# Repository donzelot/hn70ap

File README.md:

# hn70ap
Development board for modern packet radio on UHF

This repository contains sources for a few kicad projects and a NuttX board
support package for the board.

The main schematic and additional schematics and board designs are released
under the CERN OHL license.

Prerequisites
=============
 * linux (in 2017 there are many ways to get that)
 * a micro-usb cable to see the debug uart output
 * a jtag/swd adapter
 * a working openocd installation
 * an arm-none-eabi toolchain: https://launchpad.net/gcc-arm-embedded
 * to change the default configs: install kconfig-frontends
 
Mandatory: Install toolchain
============================
The arm-none-eabi toolchain provided by your distro probably does not work OK
(from experience). You may be lucky but this is not widespread enough. So we're
installing a really working toolchain.

The hardest way: compile a toolchain
------------------------------------
Hey this is a beginner guide. you dont need my guide if you are doing that. Help
yourself!

The hard way: download and install
----------------------------------

Open a bash shell console, then type commands ONE BY ONE (adapt them if you know
what you are doing):
```
$ cd $HOME
$ mkdir toolchains
$ cd toolchains
$ wget -O toolchain.tar.bz2 https://launchpad.net/gcc-arm-embedded/5.0/5-2016-q3-update/+download/gcc-arm-none-eabi-5_4-2016q3-20160926-linux.tar.bz2
$ tar jxvf toolchain.tar.bz2
$ cd $HOME
$ export PATH=$PATH:$HOME/toolchains/gcc-arm-none-eabi-5_4-2016q3/bin
```
The last line makes the ARM compiler available in your shell environment. You
can make that automatic, search the web. Otherwise you have to execute this last
line in each new shell window.

The easy way for ubuntu based distros
-------------------------------------

There is a ppa
```
sudo add-apt-repository ppa:team-gcc-arm-embedded/ppa
sudo apt-get update
sudo apt-get install gcc-arm-embedded
```

Toolchain test
--------------

You can test that the toolchain is functional by typing this command and
expecting this answer:
```
$ arm-none-eabi-gcc
arm-none-eabi-gcc: fatal error: no input files
compilation terminated.
```

If the command is not found, then the toolchain is not correctly installed and
the following will NOT work.

Optional: kconfig-frontends
===========================
Skip for now.
TODO, https://bitbucket.org/nuttx/tools, ./configure && make && make install

openocd
=======
Skip for now. TODO apt-get or ./configure && make && make install

Basic Build
===========
You need a working NuttX development environment:

```
$ mkdir nuttx
$ cd nuttx
$ git clone https://bitbucket.org/nuttx/nuttx
$ git clone https://bitbucket.org/nuttx/apps
$ cd nuttx
```
Then you can clone the board config in the proper directory
(This is NOT a submodule!)
```
$ cd configs
$ git clone https://github.com/f4grx/hn70ap
$ cd ..
```

Then choose any of the following test configurations
```
$ tools/configure.sh hn70ap/build/0_boot
```
```
$ tools/configure.sh hn70ap/build/1_memories
```
```
$ tools/configure.sh hn70ap/build/2_oled
```
And build the binary image for this board:
```
$ make
```
This should end up with an ELF binary 'nuttx', and binary images nuttx.bin

You then have to flash this binary on your board, probably with OpenOCD.

This will give you a basic shell, type help to show basic commands. This can be used to validate the behaviour of the board's CPU.

Flashing without JTAG
=====================

This will be possible later, when the bootloader is made ready. The hardware is ready to support that.
A python tool will build an update image from the nuttx elf output, and you will be able to send that image via ethernet or serial.

The bootloader is currently being written. The algorithm is as follows: At CPU startup, the external flash is initialized and searched for a firmware update, except when the button is pressed. If the update is valid, it is applied. If a failure happens, or the button has been pressed, enter a serial download mode. This mode will expect a firmware update image on the serial port and then write it to the external flash. Once done, an update attempt will be attempted after a reboot.

Advanced build
==============
More configurations will be added later that can be used to test ethernet, spi/i2c memories, etc

To modify the nuttx options type make menuconfig and mess around.

To get useful behaviour from this board you will need to add some applications that are not developed yet.

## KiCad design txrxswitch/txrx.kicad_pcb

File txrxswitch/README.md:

This folder contains a complete, stand-alone kicad project for a fast TX/RX switch that could be used with the main hn70ap circuit.

The design is experimental, in particular, I have no idea if isolation between the tx and rx branches is enough.

The project is released under the CERN OHL (schematic and board).

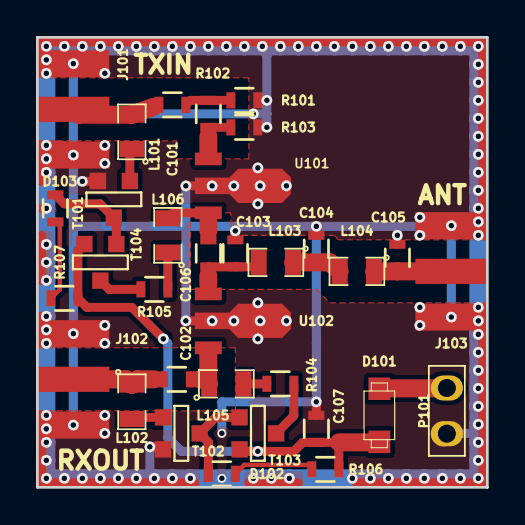
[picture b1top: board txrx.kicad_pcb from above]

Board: 2 copper layers, 25.0 x 25.0 mm, 33 parts (0 on the bottom side), 22 nets.

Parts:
C101, C102, C103, C104, C105, C106, C107: 100p; 0603_m1608
D101: DIODE; SOD123
D102, D103: LED; 0603_m1608
J101, J102, J103: SMA; SMA_EDGE_NRW
L101, L102: 3u3; 0805_m2012
L103, L104, L105, L106: LSMALL; 0805_m2012
P101: CONN_01X02; PINS-2.54-1x2
R101, R102, R103, R104, R105, R106, R107: RSMALL; 0603_m1608
T101, T102: MOSN_SMALL; SOT23GDS
T103, T104: MOSP_SMALL; SOT23GDS
U101: MMIC_SMALL; SOT89
U102: PGA-103+; SOT89

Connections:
GND: C103.1, C104.1, C105.1, C107.1, J101.2, J102.2, J103.2, P101.2, R101.2, R103.2, T101.S, T102.S, U101.2, U102.2
unnamed: C101.1, R101.1, R102.1
unnamed: C101.2, J101.1, L101.2
unnamed: C102.1, L105.1, U102.3
unnamed: C102.2, J102.1, L102.1
unnamed: C103.2, C106.1, L103.2, U102.1
unnamed: C104.2, L103.1, L104.2
unnamed: C105.2, J103.1, L104.1
unnamed: C106.2, L106.2, U101.3
unnamed: D101.A, P101.1
unnamed: D102.1, R106.2
unnamed: D102.2, T102.D, T103.G
unnamed: D103.1, R107.2
unnamed: D103.2, T101.D, T104.G
unnamed: L101.1, T101.G
unnamed: L102.2, T102.G
unnamed: L105.2, R104.1
unnamed: L106.1, R105.2
unnamed: R102.2, R103.1, U101.1
unnamed: R104.2, T103.D
unnamed: R105.1, T104.D
VDD: C107.2, D101.K, R106.1, R107.1, T103.S, T104.S

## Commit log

2017-08-01 Update README.md
    Some explanations to get started
2017-08-01 set licence to bsd 3 clause since
2017-08-01 initial files copied from stm32f429i-disco config with some renames and changes
2017-08-01 the canned config builds
2017-08-01 make Make.defs global
2017-08-01 typos
2017-08-01 Toolchain instructions
2017-08-01 details
2017-08-01 back to home dir
2017-08-01 fix toolchain path
2017-08-01 toolchain test
2017-08-01 easier toolchain options
2017-08-01 Add CERN OHL 1.2 and board readme
2017-08-01 Add existing AP project with dependencies on grx libs
2017-08-01 Remove dependencies on grx SCH libs, all components now in dedicated lib
2017-08-01 Describe the hardware connections
2017-08-01 Fix grid origin
2017-08-01 Removed dependencies on f4libs, project is now fully standalone
2017-08-02 set clock to 180 MHz
2017-08-02 define IRQ and CS lines for both radios
2017-08-02 Define radio IRQ and CS lines in readme
2017-08-02 update irq list in cpu schematic
2017-08-02 Update licence to match github detected templates
2017-08-02 actually add component library, updated with RF4463F30
2017-08-02 add rf4463f30 to radio schematic
2017-08-02 Remove useless configs
2017-08-02 More peripheral definitions
2017-08-02 Finish dual secondary radio schematic including common SDN signal, add RF4463F30 footprint
2017-08-02 Routing SPI bus to radios
2017-08-02 xtal was too close from spi bus
2017-08-02 Move cpu regulator to bring C311 to front, draw mask on back panel edge
2017-08-02 Optimizations
2017-08-03 Improve RF routing around RF4463F30 output
2017-08-03 Details added
2017-08-03 Add LEDs, major work happening in routing.
2017-08-03 add copper border on the right side
2017-08-07 Define correct peripheral pins, disable CCM heap, save latest defconfig
2017-08-07 Update LEDs pinout
2017-08-08 stop making a hex file
2017-08-08 Fix mtd partition initialization
2017-08-08 Add bootloader support and auto versioning
2017-08-09 Add footprint for wurth shielded box 20mm
2017-08-09 WIP rerouting with shielded boxes
2017-08-09 Add a TODOLIST
2017-08-09 add two LEDs for heartbeat and CPU activity
2017-08-09 Added 32khz xtal
2017-08-09 More routing and optimization Routed both CPU XTAL and VBAT connector Improved PSU fitting under shield
2017-08-09 fix RADIO_SDN near CPU pin
2017-08-09 D302 to VDD
2017-08-10 Add an application directory
2017-08-10 Add a directory for application with a readme Move all build defconfigs to their own folder Update main readme according to new folder structure
2017-08-11 Route I2C pullups, improve bottom layer clutter
2017-09-01 fix board so it can be opened with kicad 4.0.7
2017-09-11 add PDF schematic
2017-09-11 placed main radio shield and rerouted SPI bus around
2017-09-11 More SPI routing
2017-09-12 rearrange radio layout
2017-09-12 Update PP45 to use round drills for oshpark
2017-09-12 Finish schematic about RF bias, RF routing complete
2017-09-12 Update PDF schematic
2017-09-12 Missing a GND trace
2017-09-13 Fixed DRC, added ground planes, started via stitching around RF lines
2017-09-22 add a button, rename some nets, add some decoupling caps
2017-09-22 update debug interface power supply for LEDs
2017-09-26 schematic update
2017-09-28 Add pullups to ethernet lines, and re-install ferrite bead on ethernet vdda
2017-09-28 Avoid the use of extvcc, use internal compensation
2017-10-03 add test points for radio spi, add edge launch SMA for radio IO
2017-10-04 add a testpoint on mac_refclk and end launch sma to aux radio
2017-10-05 Add a ferrite bead on Vusb, thanks to f6itu for review
2017-10-05 Fix TX matching according to Silabs AN627
2017-10-26 Add a 5V LDO to power the RF4463
2017-11-24 latest changes
2017-12-01 add an UFL socket to feed an external ref to the onboard si4463
2017-12-01 add a tcxo
2017-12-08 add a test point for main radio CS signal
2017-12-11 add a test pin on IRQ
2017-12-11 add test points on ethernet lines
2017-12-13 final adjustments before paper review
2017-12-14 add gpio test points
2017-12-14 add debug uart test points
2017-12-15 add tx/rx switch project
2017-12-18 tx/rx switch complete
2017-12-21 Update README.md
    Add precisions
2017-12-21 Update README.md
    Add details
2017-12-21 Create README.md
    Add a readme for the switch
2018-01-10 disable ethernet in nsh config, move make.defs
2018-02-09 update defconfig with debug, add ocd tools
2018-02-09 update configuration names, add a readme for build configs
2018-02-10 create the startup blink configuration
2018-02-10 rename board source files add openocd script to reboot board
2018-02-11 The flash works
2018-02-11 Enable I2C3 bus
2018-02-11 add code for i2c eeprom initialization, requires i2cprom branch
2018-02-12 move make.defs to proper place, update config to build ee driver
2018-02-14 Add OLED screen initialization and example app
2018-02-14 remove incorrect includes
2018-02-15 reformat readmes, update information about nuttx configurations and i2c bus
2018-02-16 Add initialization code for radio transceivers
2018-02-16 Create board specific feature enable options
2018-02-16 start bootloader implementation
2018-02-16 cleanup kconfig
2018-02-16 add ethernet boot skeleton from somewhere else
2018-02-16 More stuff to boot ethernet
2018-02-16 Add info about enclosure
2018-02-19 radio init is functional. also more bootloader preparations
2018-02-19 last schematic updates and pdf
2018-02-20 add gpio functions to bootloader
2018-02-20 update both readmes
2018-02-20 fix indentation
2018-02-20 more improvements in gpio
2018-02-20 bootloader now writes a short message before booting user code
2018-02-21 add spi lib for bootloader - update Ethernet config PHY address
2018-02-22 Start a system daemon app to manage hardware status
2018-02-22 Prepare update algorithms
2018-02-23 add aux radio config
2018-02-23 improve spiflash
2018-02-23 build fixes
2018-02-23 read jedec id works
2018-02-23 Started bootloader spec
2018-02-23 finish boot image spec
2018-02-23 precisions and fixes
2018-02-23 fixes
2018-02-23 mkupdate tool generates the same output as objcopy
2018-02-23 finished software update tool
2018-02-23 turn useless status app into updater. add skeletons for firmware update tool and host pc update sender
2018-02-24 light green led at boot prepare mtd access from userspace
2018-02-24 rename LED definitions add MTD ops in mtdchar ioctls remove control of internal leds in the bootloader flash external red during bootloader execution, start external orange to signal download mode.
2018-03-04 updater app exchanges frames
2018-03-04 Firmware: Implement frame decoding and formatting into 256 bytes pages. Tools: detect that update app has started
2018-03-04 Software chain is not able to write an update into the ext flash via the serial port.
2018-03-05 update header name
2018-03-05 isolate update parser in a lib
2018-03-05 import crc32 code
2018-03-05 add a SHA-256 routine
2018-03-05 add a command to check the update in external flash
2018-03-05 update subcommand to erase firmware partition
2018-03-05 add boardctl support to reboot the system
2018-03-05 Bootloader checks header CRC
2018-03-06 add tlv lib to bootloader
2018-03-06 bootloader checks ext flash integrity
2018-03-06 add internal flash driver for bootloader
2018-03-06 Flash internal update is working.
2018-03-06 prepare cleanup
2018-03-06 re-add this blob after cleanup
2018-03-07 Bootloader improvements: reset flash chip before leaving bootloader, global unlock it in case we are starting from a POR and not a reboot Also add a progress indicator on the console.
2018-03-07 add a command to change speed, does not work yet
2018-03-07 Restore console settings at end of update operation
2018-03-07 Enable network monitor and dhcp nego, not working yet
2018-03-07 updater: blank check before erasing fw partition. Also fix nasty bug in bootloader spiflash waitwritecomplete().
2018-03-07 error detection in DHCP request
2018-03-07 add a skeleton for a config app - dhcp now works
2018-03-08 Enable the userled driver and use it to drive the mac link led
2018-03-08 prototype for settings app
2018-03-08 enable smartfs and start full configuration
2018-03-08 more work with config
2018-03-08 add an updater script
2018-03-08 mount storage, enable routing table
2018-03-09 Update README.md
    Add image
2018-03-09 add dummy image
2018-03-09 add board photo
2018-03-09 update photo url in readme
2018-03-09 update refactoring in progress
2018-03-11 update via TFTP is OK, also some minor cosmetic updates in update output.
2018-03-12 more enclosure details
2018-03-12 include rf support
2018-03-14 update full defconfig to enable radio and tcp keepalive
2018-03-15 add a RX test application
2018-03-15 mkupdate: customize output filenames
2018-03-15 improve spi init failure debug
2018-03-15 add a transmit test app, small fixes in rx test app
2018-03-16 progress on config app
2018-03-16 fix ip parsing
2018-03-16 Finish management of ham call and SSID
2018-03-16 add beacon app, some Kconfig improvements. Repeated transmission reveals a transmission problem where the FIFO is filled but transmission does not start.
2018-03-19 update beacon payload, add a tx delay
2018-03-19 add a dedicated RF beacon config, beacon delay 2s, define default beacon payload
2018-03-23 Add my presentation to the PocketQube workshop 2018
2018-03-27 add a timer and led driver skeleton
2018-03-28 init and use the leds drivers
2018-03-28 Enable heartbeat LED, update defconfigs
2018-03-29 WIP system init
2018-03-29 Refactor, add radio transmission code
2018-03-29 add radio RX function with green LED fix all apps to init the system before using devices. We still have a problem: when sysdaemon is used as startup, and we run additional apps, the radio device FDs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
2018-03-30 Enable support for main radio.
2018-04-12 add files for lcd management, with a font start a radio tx thread to centralize transmit requests update defconfig
2018-06-13 update defconfig
2018-06-14 more lcd and radio init
2018-06-15 fixes and simplifications
2018-06-15 prepare for tun
2018-06-15 fix tun initialization
2018-06-21 WIP tunnels
2018-06-21 fix rxt to use new cb rx api
2018-06-21 enable procfs
2018-06-21 build fixes for tunnel init
2018-06-25 spiflash and EEPROM are now mandatory
2018-06-25 remove annoying debug messages, configure procfs
2018-06-27 update defconfig to reinclude dhcp and radio
2018-06-29 reduce cpu load
2018-06-29 fixed both rx threads
2018-06-30 add defconfig
2018-07-02 correct lcd bounding box when writing strings
2018-07-04 add some misc configs
2019-01-08 update config and defaults, fixes for latest nuttx
2019-07-30 netmonitor: remove a missing logic warning. Also disable libhn70ap by default
